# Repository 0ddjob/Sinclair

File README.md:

# Sinclair
Projects for Sinclair computers (ZX80, ZX81, TS1000, TS1500, TS2068, Spectrum and clonesn such as the Minstrel 2 & 3).

## Note
These projects maybe work-in-progress and thus not completed or fully tested!

# [TS1500 Extender](/TS1500_Extender)
The Timex Sinclair TS1500 is a 16KB ZX81/TS1000 in a Spectrum-style case.  As such the expansion port can use full-width expansions due to the power & cassette ports.  This project aims to create an extender to allow full-width expansion (i.e. ZXpand) to be used.

## Status
22-May-2025: Work in progress<br>

# [ZX80 Gaming Keyboard](/ZX80_Gaming_Keyboard)
The cursor keys on a ZX80/ZX81 are the 5/6/7/8 numeric keys along the top row.  My simple brain can't readily adapt to this in games like ZX80 KONG or PACMAN so this is just a ZX80/ZX81 compatible keyboard with additional cursor keys.  Designed initially for use with the Minstrel 2 computer (ZX80), but can also be used with the ZX80, Minstrel 3/ZX81 and Minstrel 4th/Jupiter Ace.

## Video
- [Minstrel 2 (Sinclair ZX80 Clone): Part 3 (Gaming Keyboard)](https://youtu.be/veES_CpFuDQ)
- [Gaming Keyboard for ZX80/ZX81/Minstrel/Jupiter Ace: Part 1 (Minstrel 2 Test)](https://youtu.be/O0Em2sR0H4w)

## Status
22-May-2025: Sent to PCBWAY for test boards<br>
14-Jun-2025: Tested, errors found & fixed, PCB layout will be corrected<br>
16-Jun-2025: Revised PCB layout submitted to PCBWAY for test fabrication<br>
27-Jun-2025: Rev. B keyboard tested mostly ok, dedicated RUBOUT key not working though<br>

# [ZX80 Pixel Synch](/ZX80_Pixel_Sync)
Small daughterboard to fix the [ZX80's pixel synchronisation](http://blog.tynemouthsoftware.co.uk/2022/09/minstrel-2-pixel-synchronisation-part-1.html) issue on the Minstrel 2 computer v2.8 or earlier.  I have a v2.6 board.  

## Video
[Minstrel 2 (Sinclair ZX80 Clone): Part 2 (Pixel Synch. Issue)](https://youtu.be/O-Urgigq2Vk)

## Status
7-May-2025: Sent to PCBWAY for test boards<br>
23-May-2025: Tested successfully on my Minstrel v2.6 board! Big improvement<br>
24-May-2025: Revised layout in Rev. B, handrouted like a big boy!<br>

# [ZX81 Centronics](/ZX81_Centronics)
Recreating a DIY centronics interface from German computer magazine c't.<br>

## Status
17-Sept-2023: Completed it seems, but not yet tested

# [ZX81 RAM Upgrade](/ZX81_RAM_Upgrade)
Yes, yes, it's been done many times before.  Planning a few different versions: 16KB for standard ZX81/TS1000, 32KB with vLA1, 32KB with own PLD.

## Status
10-Sept-2023: Designed & tested<br>
22-May-2025: Don't like the original design, will re-design<br>

# [Z88 Serial Port Converter (DE9-to-DB25)](/Z88_Serial_DE9-to-DB25)
I'm finally getting my hands on a Cambridge Computers Z88.  I realised that the [Universal Backpack Drive (UBPD)](https://www.soigeneris.com/universal-backpack-drive) I have for the NEC-PC8201A will also work on the Z88 but requires a converter board.  It's possible to order one from Soigeneris when you order a UBPD and there is an existing design available on [Github](https://github.com/bkw777/Z88_RS232), but I thought I'd also have a crack at it.

## Video
[Cambridge Computer Z88: Part 2 (Backpack Drive - First Attempt)](https://youtu.be/SjToMHrZwcI)

## Status
30-Jun-2025: Tested successfully<br>

# [Z88 Serial Port Converter (DE9-to-DE9)](/Z88_Serial_DE9_Converter)
Simple board to convert Z88 DE9 serial port to standard DE9 to use with Serial-to-USB converter, for example.

## Status
1-Jul-2025: Initial design<br>

# [Z88 Mechanical Keyboard](/Z88_Mechanical_Keyboard)
The original keyboard on my Z88 seems a bit flaky - let's try designing a nice, modern replacement.

## Status
25-Jul-2025: Rev. A board tested successfully, some tweaks needed.<br>

# [VDrive Serial Interface for Z88](/VDriveZ88_Serial_Converter)
Serial interface converter for the Z88 to use a VDrive.

## Status
9-Aug-2025: Initial design completed

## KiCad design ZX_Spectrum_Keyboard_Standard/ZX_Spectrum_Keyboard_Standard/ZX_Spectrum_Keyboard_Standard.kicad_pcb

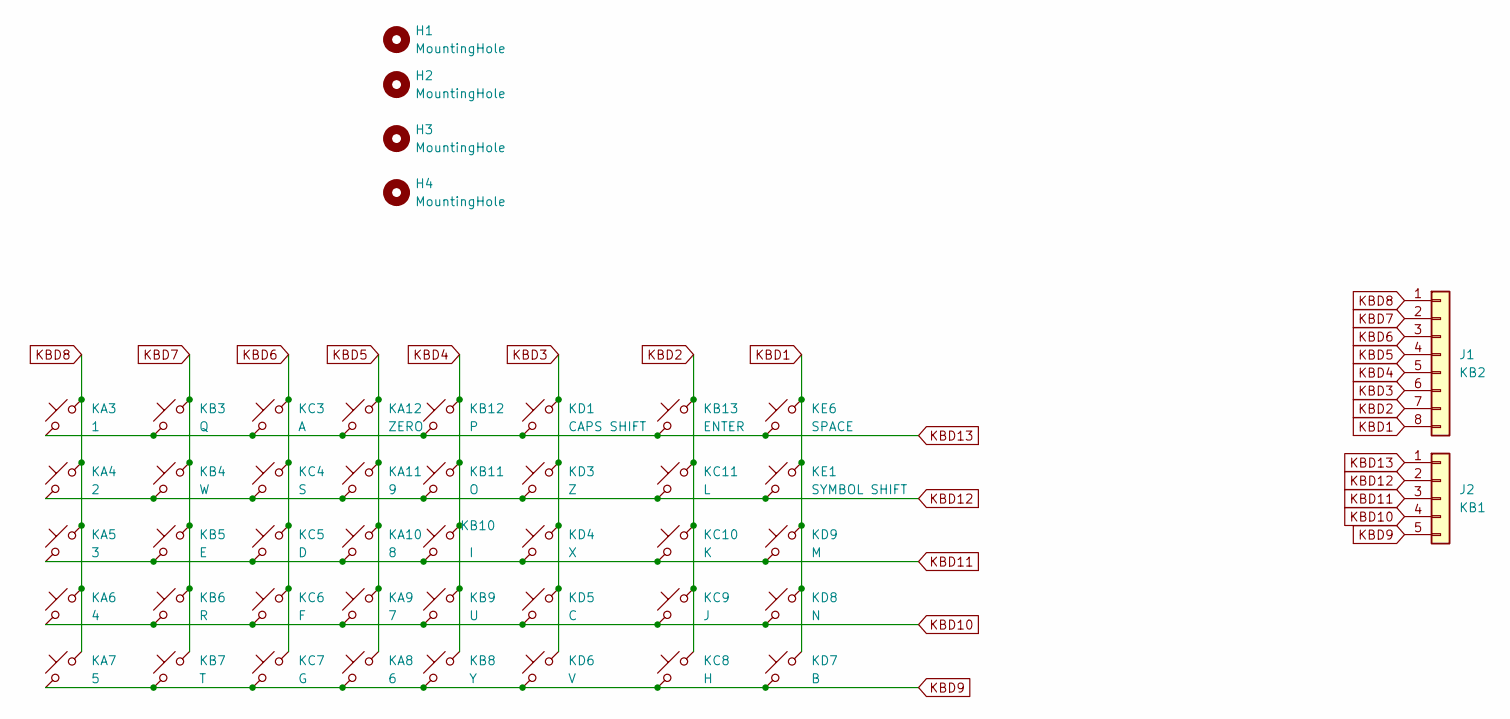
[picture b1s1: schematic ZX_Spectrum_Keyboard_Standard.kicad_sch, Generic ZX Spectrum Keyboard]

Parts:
H1, H2, H3, H4: MountingHole; MountingHole_3.2mm_M3
J1: KB2; PinHeader_1x08_P2.54mm_Vertical
J2: KB1; PinHeader_1x05_P2.54mm_Vertical
KA3: 1; SW_Gateron_LowProfile_THT
KA4: 2; SW_Gateron_LowProfile_THT
KA5: 3; SW_Gateron_LowProfile_THT
KA6: 4; SW_Gateron_LowProfile_THT
KA7: 5; SW_Gateron_LowProfile_THT
KA8: 6; SW_Gateron_LowProfile_THT
KA9: 7; SW_Gateron_LowProfile_THT
KA10: 8; SW_Gateron_LowProfile_THT
KA11: 9; SW_Gateron_LowProfile_THT
KA12: ZERO; SW_Gateron_LowProfile_THT
KB3: Q; SW_Gateron_LowProfile_THT
KB4: W; SW_Gateron_LowProfile_THT
KB5: E; SW_Gateron_LowProfile_THT
KB6: R; SW_Gateron_LowProfile_THT
KB7: T; SW_Gateron_LowProfile_THT
KB8: Y; SW_Gateron_LowProfile_THT
KB9: U; SW_Gateron_LowProfile_THT
KB10: I; SW_Gateron_LowProfile_THT
KB11: O; SW_Gateron_LowProfile_THT
KB12: P; SW_Gateron_LowProfile_THT
KB13: ENTER; SW_Gateron_LowProfile_THT
KC3: A; SW_Gateron_LowProfile_THT
KC4: S; SW_Gateron_LowProfile_THT
KC5: D; SW_Gateron_LowProfile_THT
KC6: F; SW_Gateron_LowProfile_THT
KC7: G; SW_Gateron_LowProfile_THT
KC8: H; SW_Gateron_LowProfile_THT
KC9: J; SW_Gateron_LowProfile_THT
KC10: K; SW_Gateron_LowProfile_THT
KC11: L; SW_Gateron_LowProfile_THT
KD1: CAPS SHIFT; SW_Gateron_LowProfile_THT
KD3: Z; SW_Gateron_LowProfile_THT
KD4: X; SW_Gateron_LowProfile_THT
KD5: C; SW_Gateron_LowProfile_THT
KD6: V; SW_Gateron_LowProfile_THT
KD7: B; SW_Gateron_LowProfile_THT
KD8: N; SW_Gateron_LowProfile_THT
KD9: M; SW_Gateron_LowProfile_THT
KE1: SYMBOL SHIFT; SW_Gateron_LowProfile_THT
KE6: SPACE; SW_Gateron_LowProfile_THT

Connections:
KBD1: J1.8, KD7.2, KD8.2, KD9.2, KE1.2, KE6.2
KBD2: J1.7, KB13.2, KC8.2, KC9.2, KC10.2, KC11.2
KBD3: J1.6, KD1.2, KD3.2, KD4.2, KD5.2, KD6.2
KBD4: J1.5, KB8.2, KB9.2, KB10.2, KB11.2, KB12.2
KBD5: J1.4, KA8.2, KA9.2, KA10.2, KA11.2, KA12.2
KBD6: J1.3, KC3.2, KC4.2, KC5.2, KC6.2, KC7.2
KBD7: J1.2, KB3.2, KB4.2, KB5.2, KB6.2, KB7.2
KBD8: J1.1, KA3.2, KA4.2, KA5.2, KA6.2, KA7.2
KBD9: J2.5, KA7.1, KA8.1, KB7.1, KB8.1, KC7.1, KC8.1, KD6.1, KD7.1
KBD10: J2.4, KA6.1, KA9.1, KB6.1, KB9.1, KC6.1, KC9.1, KD5.1, KD8.1
KBD11: J2.3, KA5.1, KA10.1, KB5.1, KB10.1, KC5.1, KC10.1, KD4.1, KD9.1
KBD12: J2.2, KA4.1, KA11.1, KB4.1, KB11.1, KC4.1, KC11.1, KD3.1, KE1.1
KBD13: J2.1, KA3.1, KA12.1, KB3.1, KB12.1, KB13.1, KC3.1, KD1.1, KE6.1

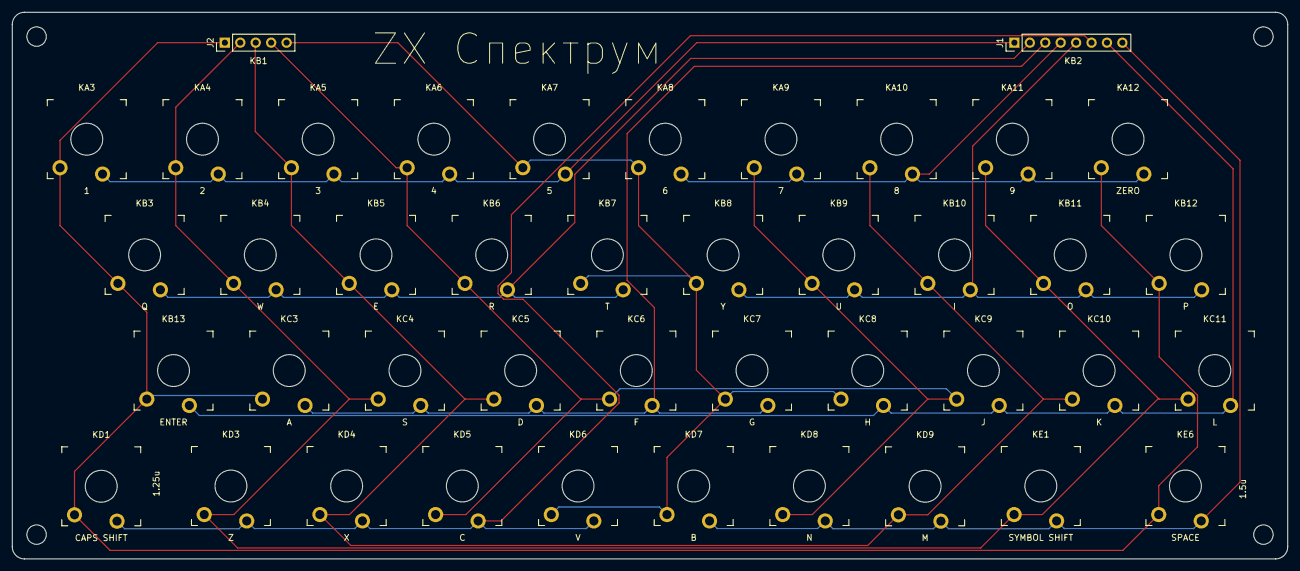
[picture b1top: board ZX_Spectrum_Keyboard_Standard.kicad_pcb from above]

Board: 2 copper layers, 210.0 x 90.0 mm, 46 parts (0 on the bottom side), 13 nets.

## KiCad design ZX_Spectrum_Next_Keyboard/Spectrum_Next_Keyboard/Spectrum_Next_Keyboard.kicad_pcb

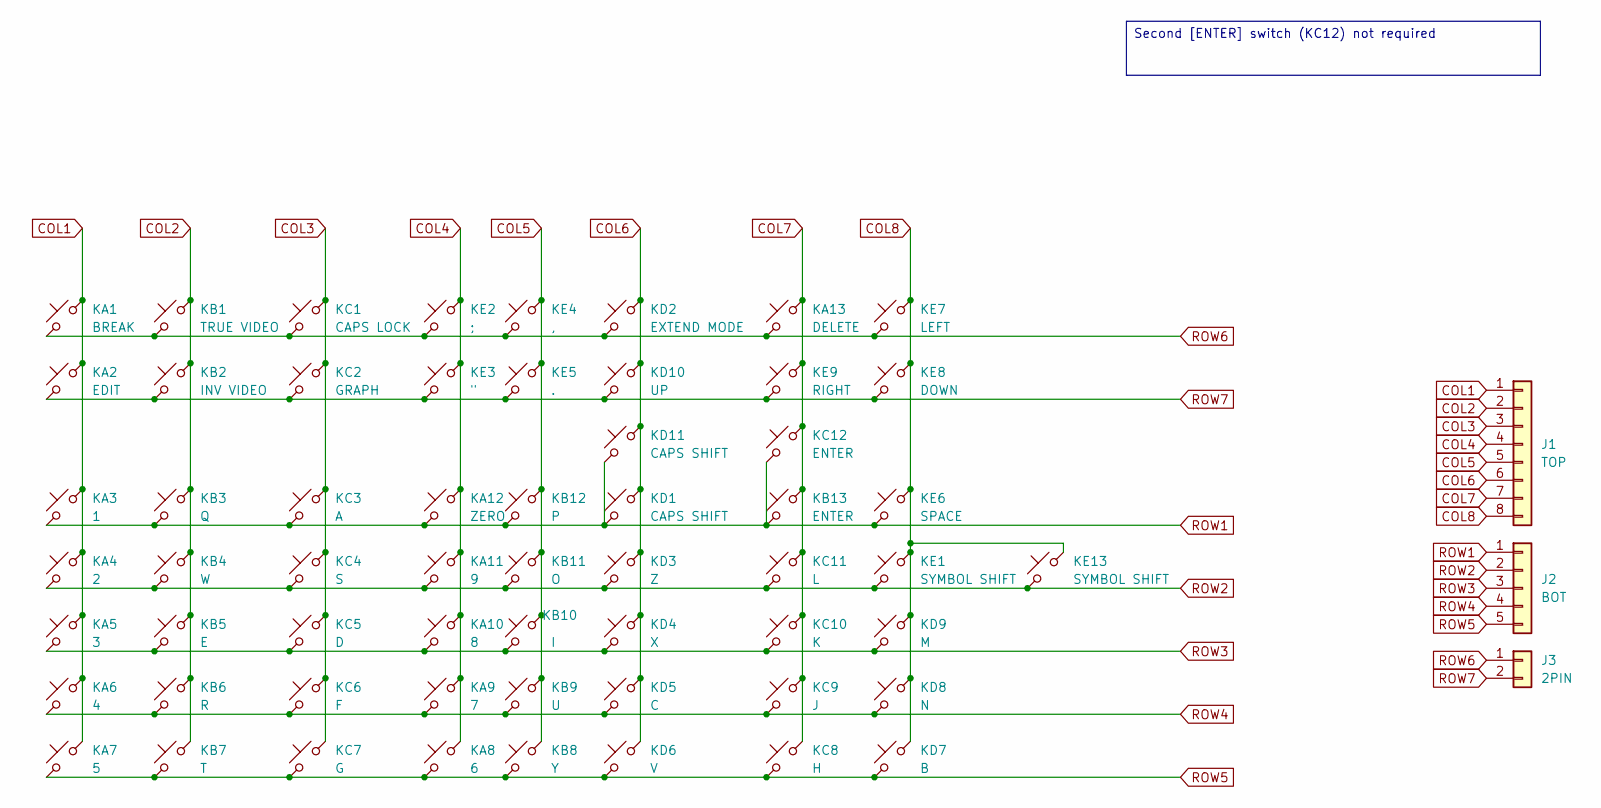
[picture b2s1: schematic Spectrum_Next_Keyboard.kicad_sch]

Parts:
J1: TOP; PinHeader_1x08_P2.54mm_Vertical
J2: BOT; PinHeader_1x05_P2.54mm_Vertical
J3: 2PIN; PinHeader_1x02_P2.54mm_Vertical
KA1: BREAK; SW_Gateron_LowProfile_THT
KA2: EDIT; SW_Gateron_LowProfile_THT
KA3: 1; SW_Gateron_LowProfile_THT
KA4: 2; SW_Gateron_LowProfile_THT
KA5: 3; SW_Gateron_LowProfile_THT
KA6: 4; SW_Gateron_LowProfile_THT
KA7: 5; SW_Gateron_LowProfile_THT
KA8: 6; SW_Gateron_LowProfile_THT
KA9: 7; SW_Gateron_LowProfile_THT
KA10: 8; SW_Gateron_LowProfile_THT
KA11: 9; SW_Gateron_LowProfile_THT
KA12: ZERO; SW_Gateron_LowProfile_THT
KA13: DELETE; SW_Gateron_LowProfile_THT
KB1: TRUE VIDEO; SW_Gateron_LowProfile_THT
KB2: INV VIDEO; SW_Gateron_LowProfile_THT
KB3: Q; SW_Gateron_LowProfile_THT
KB4: W; SW_Gateron_LowProfile_THT
KB5: E; SW_Gateron_LowProfile_THT
KB6: R; SW_Gateron_LowProfile_THT
KB7: T; SW_Gateron_LowProfile_THT
KB8: Y; SW_Gateron_LowProfile_THT
KB9: U; SW_Gateron_LowProfile_THT
KB10: I; SW_Gateron_LowProfile_THT
KB11: O; SW_Gateron_LowProfile_THT
KB12: P; SW_Gateron_LowProfile_THT
KB13: ENTER; SW_Gateron_LowProfile_THT
KC1: CAPS LOCK; SW_Gateron_LowProfile_THT
KC2: GRAPH; SW_Gateron_LowProfile_THT
KC3: A; SW_Gateron_LowProfile_THT
KC4: S; SW_Gateron_LowProfile_THT
KC5: D; SW_Gateron_LowProfile_THT
KC6: F; SW_Gateron_LowProfile_THT
KC7: G; SW_Gateron_LowProfile_THT
KC8: H; SW_Gateron_LowProfile_THT
KC9: J; SW_Gateron_LowProfile_THT
KC10: K; SW_Gateron_LowProfile_THT
KC11: L; SW_Gateron_LowProfile_THT
KC12: ENTER; SW_Gateron_LowProfile_THT
KD1, KD11: CAPS SHIFT; SW_Gateron_LowProfile_THT
KD2: EXTEND MODE; SW_Gateron_LowProfile_THT
KD3: Z; SW_Gateron_LowProfile_THT
KD4: X; SW_Gateron_LowProfile_THT
KD5: C; SW_Gateron_LowProfile_THT
KD6: V; SW_Gateron_LowProfile_THT
KD7: B; SW_Gateron_LowProfile_THT
KD8: N; SW_Gateron_LowProfile_THT
KD9: M; SW_Gateron_LowProfile_THT
KD10: UP; SW_Gateron_LowProfile_THT
KE1, KE13: SYMBOL SHIFT; SW_Gateron_LowProfile_THT
KE2: ;; SW_Gateron_LowProfile_THT
KE3: "; SW_Gateron_LowProfile_THT
KE4: ,; SW_Gateron_LowProfile_THT
KE5: .; SW_Gateron_LowProfile_THT
KE6: SPACE; SW_Gateron_LowProfile_THT
KE7: LEFT; SW_Gateron_LowProfile_THT
KE8: DOWN; SW_Gateron_LowProfile_THT
KE9: RIGHT; SW_Gateron_LowProfile_THT

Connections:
COL1: J1.1, KA1.2, KA2.2, KA3.2, KA4.2, KA5.2, KA6.2, KA7.2
COL2: J1.2, KB1.2, KB2.2, KB3.2, KB4.2, KB5.2, KB6.2, KB7.2
COL3: J1.3, KC1.2, KC2.2, KC3.2, KC4.2, KC5.2, KC6.2, KC7.2
COL4: J1.4, KA8.2, KA9.2, KA10.2, KA11.2, KA12.2, KE2.2, KE3.2
COL5: J1.5, KB8.2, KB9.2, KB10.2, KB11.2, KB12.2, KE4.2, KE5.2
COL6: J1.6, KD1.2, KD2.2, KD3.2, KD4.2, KD5.2, KD6.2, KD10.2, KD11.2
COL7: J1.7, KA13.2, KB13.2, KC8.2, KC9.2, KC10.2, KC11.2, KC12.2, KE9.2
COL8: J1.8, KD7.2, KD8.2, KD9.2, KE1.2, KE6.2, KE7.2, KE8.2, KE13.2
ROW1: J2.1, KA3.1, KA12.1, KB3.1, KB12.1, KB13.1, KC3.1, KC12.1, KD1.1, KD11.1, KE6.1
ROW2: J2.2, KA4.1, KA11.1, KB4.1, KB11.1, KC4.1, KC11.1, KD3.1, KE1.1, KE13.1
ROW3: J2.3, KA5.1, KA10.1, KB5.1, KB10.1, KC5.1, KC10.1, KD4.1, KD9.1
ROW4: J2.4, KA6.1, KA9.1, KB6.1, KB9.1, KC6.1, KC9.1, KD5.1, KD8.1
ROW5: J2.5, KA7.1, KA8.1, KB7.1, KB8.1, KC7.1, KC8.1, KD6.1, KD7.1
ROW6: J3.1, KA1.1, KA13.1, KB1.1, KC1.1, KD2.1, KE2.1, KE4.1, KE7.1
ROW7: J3.2, KA2.1, KB2.1, KC2.1, KD10.1, KE3.1, KE5.1, KE8.1, KE9.1

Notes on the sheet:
Second [ENTER] switch (KC12) not required

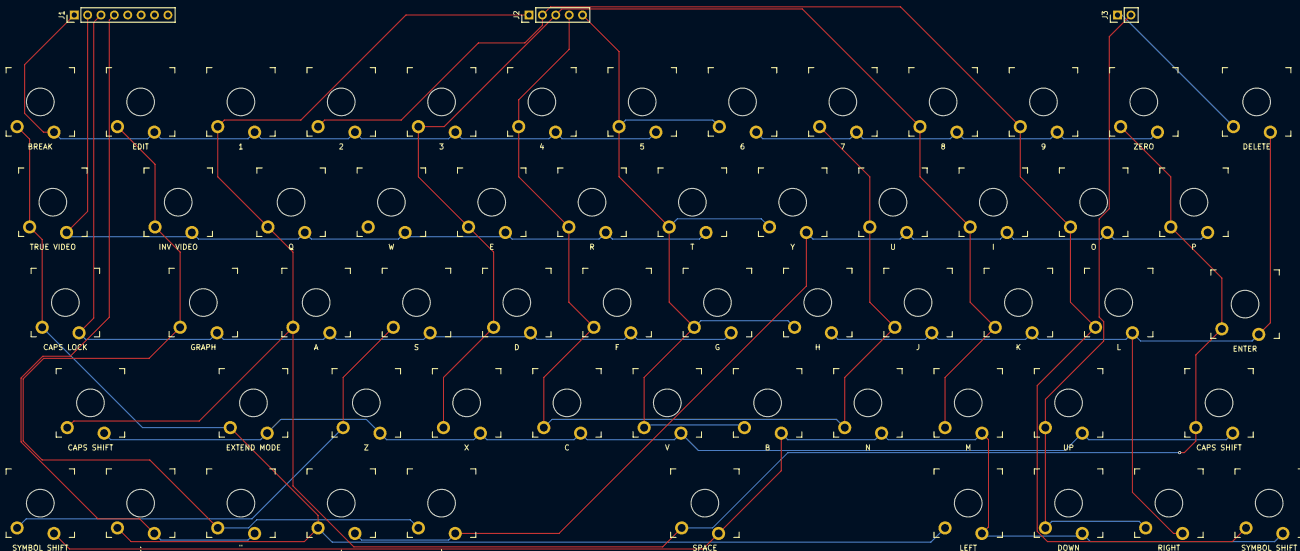
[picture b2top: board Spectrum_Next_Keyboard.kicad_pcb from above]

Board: 2 copper layers, 61 parts (0 on the bottom side), 15 nets.

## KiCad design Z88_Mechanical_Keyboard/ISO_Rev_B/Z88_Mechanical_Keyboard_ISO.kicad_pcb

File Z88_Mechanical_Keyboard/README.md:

# Z88 Mechanical Keyboard
I've not had too much luck with the keyboard on my Z88 - seems a bit flaky after 40-odd years.  So I thought I'd try to create a mechanical replacement.<br>

I've modified the layout slightly to improve the arrangement - the cursors are now a "proper" inverted-T layout.<br>

## Layout
The layout almost matches a modern set of keycaps, apart from the custom ones.<br>
By this, I mean the SHIFTED characters on each key match a modern keyboard so a generic set of key caps, plus some blanks, should work.<br>

## Changes From Original Z88 Layout
The reason for these changes are either to improve the layout (cursors) or to simplify getting key caps (CAPS LOCK & DIAMOND)
- (Rev. A) Cursors are now an inverted-T
- (Rev. B) CAPS LOCK moved to standard location between TAB and LH SHIFT and is now 1.75u (a standard size in key cap sets)
- (Rev. B) DIAMOND moved to original DOWN cursor location (bottom right) and is now 1u (can use a blank)
- (Rev. C) Possibly external version via Z88 expansion port featuring switchable on/off backlit keys ... ?

## Construction
The board is designed to use Gateron Low Profile (KS-33) type key switches with Cherry MX-style key caps.<br>

- 64 key switches (Gateron KS-33)
- 53 x 1u key caps
- 5 x 1u blank (INDEX, MENU, HELP, SQUARE, DIAMOND)
- 1 x 1.25x2u (ISO ENTER)
- 1 x 1.5u (TAB)
- 1 x 1.75u (CAPS LOCK)
- 2 x 2u (SHIFT)
- 1 x 7u (SPACE)
- (Optional) Stabiliser for 7u SPACE bar? (must work with Gateron low-profile)
- 2 x 8-pin thin film connectors (e.g. TE Connectivity/AMP 5-520314-8 or similar)
- 2 x 8-pin strips of thin film cables (e.g. Parlex PSR1635-08 or similar)

I've not been able to find suitable PCB-mount stabilisers yet.<br>

## Related Videos
- [Schematic & PCB layout](https://youtu.be/C3n-ExND1uk)
- [Track routing & final touches](https://youtu.be/aaBBvU5d50o)
- [Testing the Rev. A PCB](https://youtu.be/vxIY81ir3Ao)
- [Testing the Rev. B PCB](https://youtu.be/KMXMAZTbPG8)

## Further Work To Do 
### Rev. C
- Create an external version (no changes required to Z88) connecting via Z88 expansion port
- Z88 expansion port connector still available?

## Status
1-Jul-2025: Work in progress<br>
3-Jul-2025: Added 6.25u space bar layout<br>
4-Jul-2025: Added inverted-T cursor layout<br>
5-Jul-2025: Inverted-T cursor design routed, ready for test fabrication<br>
7-Jul-2025: Design tweaked, sent to PCBWAY for test fabrication<br>
12-Jul-2025: Test PCBs shipped from PCBWAY<br>
25-Jul-2025: Test PCBs arrived, working!!, need to adjust size of PCB slightly ... maybe (see [video](https://youtu.be/vxIY81ir3Ao))<br>
26-Jul-2025: Started work on Rev. B<br>
31-Jul-2025: Completed Rev. B changes<br>
1-Aug-2025: Submitted to PCBway<br>
5-Aug-2025: Rev. B PCBs shipped from PCBway<br>
15-Aug-2025: Rev. B test PCBs arrived & tested, almost perfect.<br>

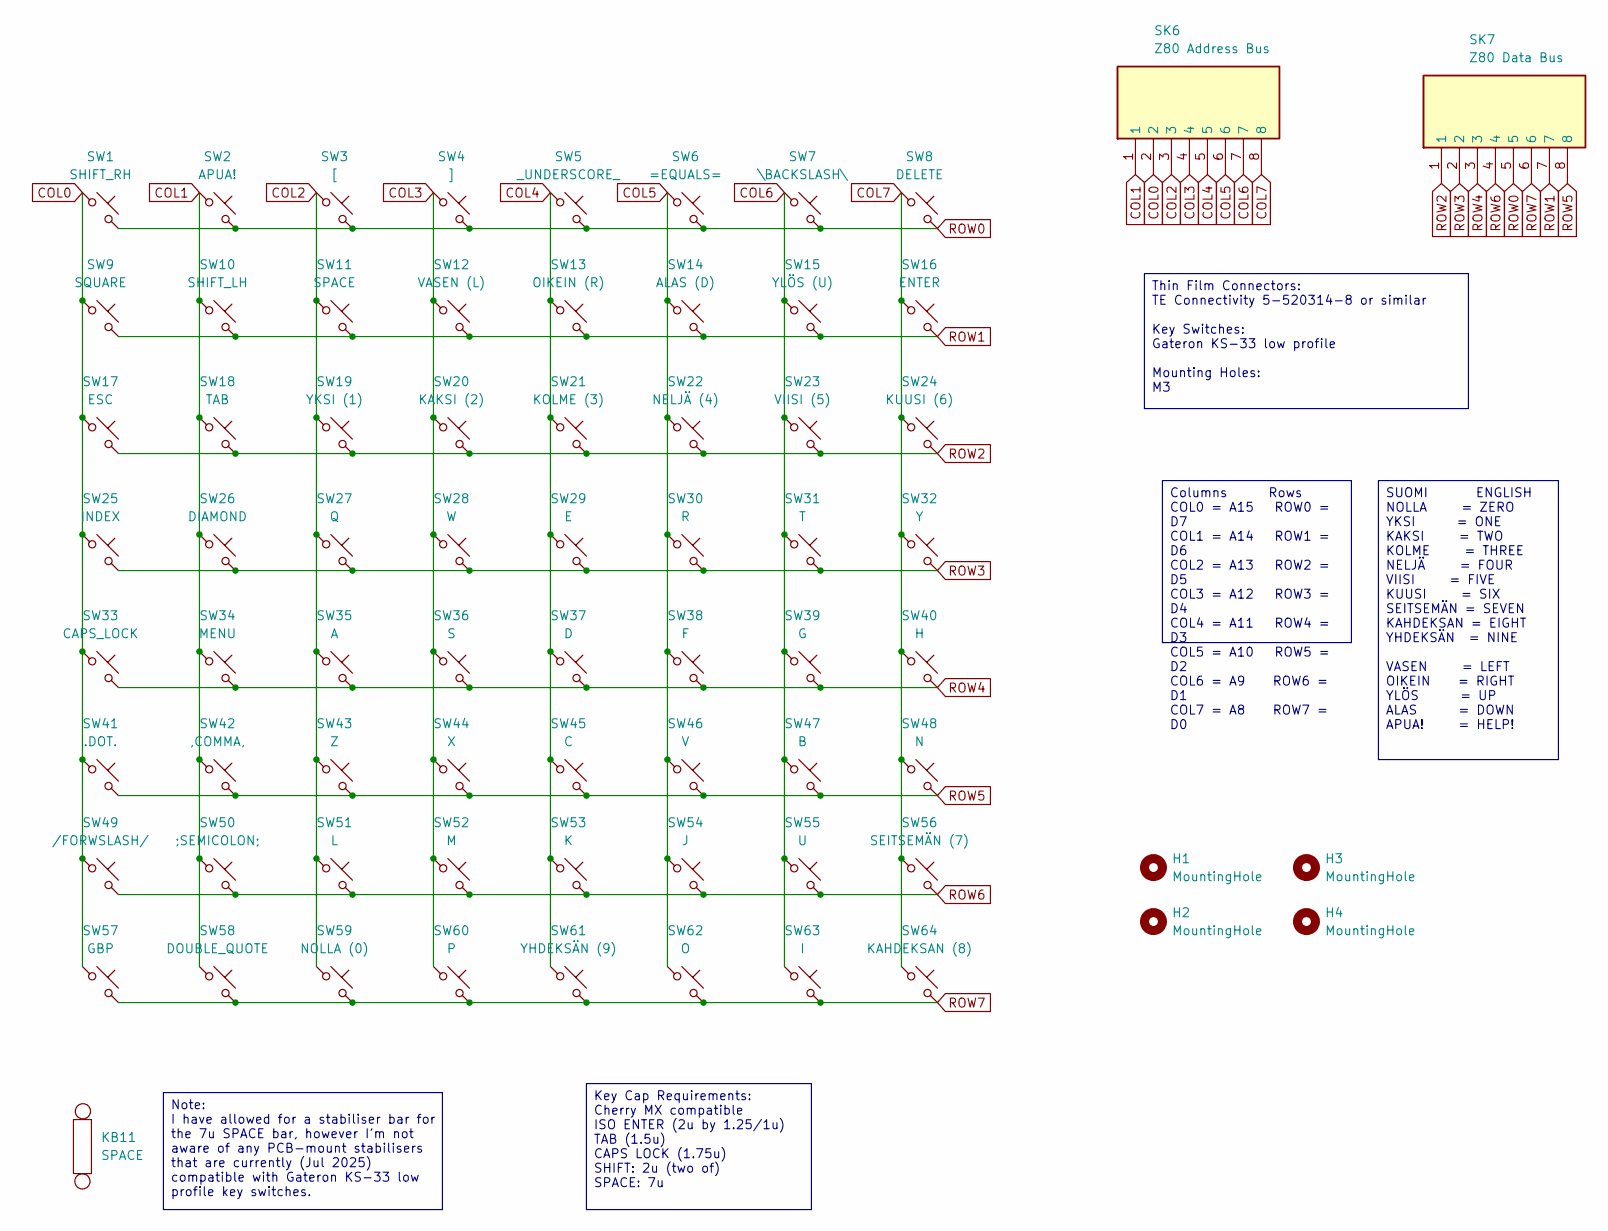
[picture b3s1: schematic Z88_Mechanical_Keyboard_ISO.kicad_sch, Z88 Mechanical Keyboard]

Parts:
H1, H2, H3, H4: MountingHole; MountingHole_3.2mm_M3
KB11: SPACE; Stabilizer_Cherry_MX_7.00u
SK6: Z80 Address Bus; 55203148; Mouser Part Number 571-5-520314-8
SK7: Z80 Data Bus; 55203148; Mouser Part Number 571-5-520314-8
SW1: SHIFT_RH; SW_Gateron_LowProfile_THT
SW2: APUA!; SW_Gateron_LowProfile_THT
SW3: [; SW_Gateron_LowProfile_THT
SW4: ]; SW_Gateron_LowProfile_THT
SW5: _UNDERSCORE_; SW_Gateron_LowProfile_THT
SW6: =EQUALS=; SW_Gateron_LowProfile_THT
SW7: \BACKSLASH\; SW_Gateron_LowProfile_THT
SW8: DELETE; SW_Gateron_LowProfile_THT
SW9: SQUARE; SW_Gateron_LowProfile_THT
SW10: SHIFT_LH; SW_Gateron_LowProfile_THT
SW11: SPACE; SW_Gateron_LowProfile_THT
SW12: VASEN (L); SW_Gateron_LowProfile_THT
SW13: OIKEIN (R); SW_Gateron_LowProfile_THT
SW14: ALAS (D); SW_Gateron_LowProfile_THT
SW15: YLÖS (U); SW_Gateron_LowProfile_THT
SW16: ENTER; SW_Gateron_LowProfile_THT
SW17: ESC; SW_Gateron_LowProfile_THT
SW18: TAB; SW_Gateron_LowProfile_THT
SW19: YKSI (1); SW_Gateron_LowProfile_THT
SW20: KAKSI (2); SW_Gateron_LowProfile_THT
SW21: KOLME (3); SW_Gateron_LowProfile_THT
SW22: NELJÄ (4); SW_Gateron_LowProfile_THT
SW23: VIISI (5); SW_Gateron_LowProfile_THT
SW24: KUUSI (6); SW_Gateron_LowProfile_THT
SW25: INDEX; SW_Gateron_LowProfile_THT
SW26: DIAMOND; SW_Gateron_LowProfile_THT
SW27: Q; SW_Gateron_LowProfile_THT
SW28: W; SW_Gateron_LowProfile_THT
SW29: E; SW_Gateron_LowProfile_THT
SW30: R; SW_Gateron_LowProfile_THT
SW31: T; SW_Gateron_LowProfile_THT
SW32: Y; SW_Gateron_LowProfile_THT
SW33: CAPS_LOCK; SW_Gateron_LowProfile_THT
SW34: MENU; SW_Gateron_LowProfile_THT
SW35: A; SW_Gateron_LowProfile_THT
SW36: S; SW_Gateron_LowProfile_THT
SW37: D; SW_Gateron_LowProfile_THT
SW38: F; SW_Gateron_LowProfile_THT
SW39: G; SW_Gateron_LowProfile_THT
SW40: H; SW_Gateron_LowProfile_THT
SW41: .DOT.; SW_Gateron_LowProfile_THT
SW42: ,COMMA,; SW_Gateron_LowProfile_THT
SW43: Z; SW_Gateron_LowProfile_THT
SW44: X; SW_Gateron_LowProfile_THT
SW45: C; SW_Gateron_LowProfile_THT
SW46: V; SW_Gateron_LowProfile_THT
SW47: B; SW_Gateron_LowProfile_THT
SW48: N; SW_Gateron_LowProfile_THT
SW49: /FORWSLASH/; SW_Gateron_LowProfile_THT
SW50: ;SEMICOLON;; SW_Gateron_LowProfile_THT
SW51: L; SW_Gateron_LowProfile_THT
SW52: M; SW_Gateron_LowProfile_THT
SW53: K; SW_Gateron_LowProfile_THT
SW54: J; SW_Gateron_LowProfile_THT
SW55: U; SW_Gateron_LowProfile_THT
SW56: SEITSEMÄN (7); SW_Gateron_LowProfile_THT
SW57: GBP; SW_Gateron_LowProfile_THT
SW58: DOUBLE_QUOTE; SW_Gateron_LowProfile_THT
SW59: NOLLA (0); SW_Gateron_LowProfile_THT
SW60: P; SW_Gateron_LowProfile_THT
SW61: YHDEKSÄN (9); SW_Gateron_LowProfile_THT
SW62: O; SW_Gateron_LowProfile_THT
SW63: I; SW_Gateron_LowProfile_THT
SW64: KAHDEKSAN (8); SW_Gateron_LowProfile_THT

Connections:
COL0: SK6.2, SW1.1, SW9.1, SW17.1, SW25.1, SW33.1, SW41.1, SW49.1, SW57.1
COL1: SK6.1, SW2.1, SW10.1, SW18.1, SW26.1, SW34.1, SW42.1, SW50.1, SW58.1
COL2: SK6.3, SW3.1, SW11.1, SW19.1, SW27.1, SW35.1, SW43.1, SW51.1, SW59.1
COL3: SK6.4, SW4.1, SW12.1, SW20.1, SW28.1, SW36.1, SW44.1, SW52.1, SW60.1
COL4: SK6.5, SW5.1, SW13.1, SW21.1, SW29.1, SW37.1, SW45.1, SW53.1, SW61.1
COL5: SK6.6, SW6.1, SW14.1, SW22.1, SW30.1, SW38.1, SW46.1, SW54.1, SW62.1
COL6: SK6.7, SW7.1, SW15.1, SW23.1, SW31.1, SW39.1, SW47.1, SW55.1, SW63.1
COL7: SK6.8, SW8.1, SW16.1, SW24.1, SW32.1, SW40.1, SW48.1, SW56.1, SW64.1
ROW0: SK7.5, SW1.2, SW2.2, SW3.2, SW4.2, SW5.2, SW6.2, SW7.2, SW8.2
ROW1: SK7.7, SW9.2, SW10.2, SW11.2, SW12.2, SW13.2, SW14.2, SW15.2, SW16.2
ROW2: SK7.1, SW17.2, SW18.2, SW19.2, SW20.2, SW21.2, SW22.2, SW23.2, SW24.2
ROW3: SK7.2, SW25.2, SW26.2, SW27.2, SW28.2, SW29.2, SW30.2, SW31.2, SW32.2
ROW4: SK7.3, SW33.2, SW34.2, SW35.2, SW36.2, SW37.2, SW38.2, SW39.2, SW40.2
ROW5: SK7.8, SW41.2, SW42.2, SW43.2, SW44.2, SW45.2, SW46.2, SW47.2, SW48.2
ROW6: SK7.4, SW49.2, SW50.2, SW51.2, SW52.2, SW53.2, SW54.2, SW55.2, SW56.2
ROW7: SK7.6, SW57.2, SW58.2, SW59.2, SW60.2, SW61.2, SW62.2, SW63.2, SW64.2

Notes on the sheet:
Note: I have allowed for a stabiliser bar for the 7u SPACE bar, however I'm not aware of any PCB-mount stabilisers that are currently (Jul 2025) compatible with Gateron KS-33 low profile key switches.
Key Cap Requirements: Cherry MX compatible ISO ENTER (2u by 1.25/1u) TAB (1.5u) CAPS LOCK (1.75u) SHIFT: 2u (two of) SPACE: 7u
Thin Film Connectors: TE Connectivity 5-520314-8 or similar Key Switches: Gateron KS-33 low profile Mounting Holes: M3
SUOMI ENGLISH NOLLA = ZERO YKSI = ONE KAKSI = TWO KOLME = THREE NELJÄ = FOUR VIISI = FIVE KUUSI = SIX SEITSEMÄN = SEVEN KAHDEKSAN = EIGHT YHDEKSÄN = NINE VASEN = LEFT OIKEIN = RIGHT YLÖS = UP ALAS = DOWN APUA! = HELP!
Columns Rows COL0 = A15 ROW0 = D7 COL1 = A14 ROW1 = D6 COL2 = A13 ROW2 = D5 COL3 = A12 ROW3 = D4 COL4 = A11 ROW4 = D3 COL5 = A10 ROW5 = D2 COL6 = A9 ROW6 = D1 COL7 = A8 ROW7 = D0

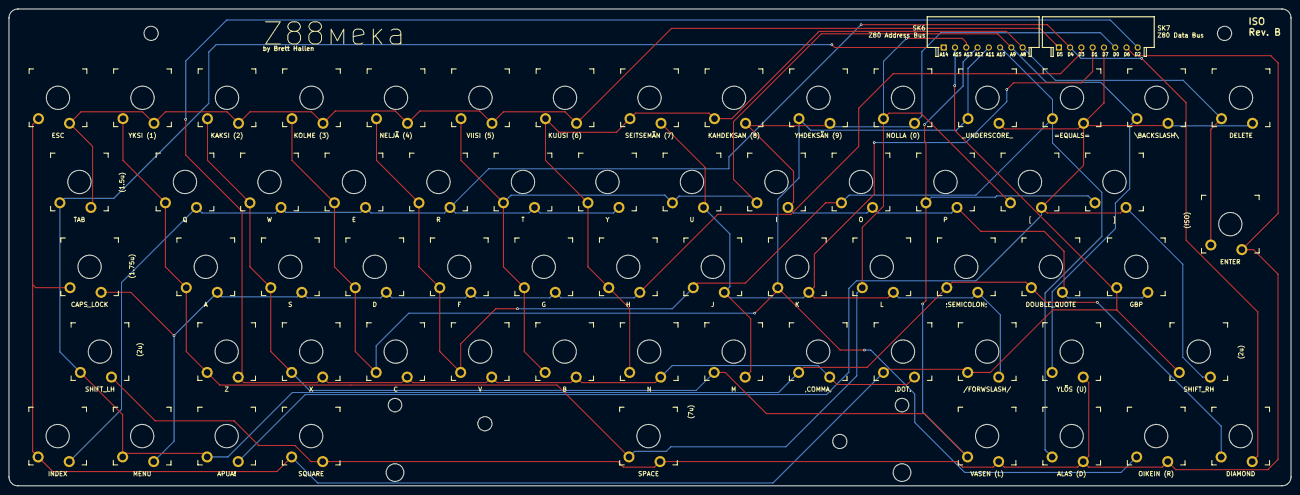
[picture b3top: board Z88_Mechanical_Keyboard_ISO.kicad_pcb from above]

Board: 2 copper layers, 289.0 x 107.5 mm, 71 parts (0 on the bottom side), 16 nets.

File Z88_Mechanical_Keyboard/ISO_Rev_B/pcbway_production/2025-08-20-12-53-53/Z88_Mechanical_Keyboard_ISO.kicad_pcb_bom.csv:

Designator,Quantity,Value,Footprint,Package,MPN,DNP,Mount_Type,Description,Height,Mouser Part Number,Mouser Price/Stock,Manufacturer_Name
KB11,1,SPACE,Stabilizer_Cherry_MX_7.00u,,,,tht,,,,,
SK6,1,Z80 Address Bus,55203148,,5-520314-8,,tht,TRIOMATE ASSY H 8P L=2.54 LDFR,4.83,571-5-520314-8,https://www.mouser.co.uk/ProductDetail/TE-Connectivity-AMP/5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,TE Connectivity
SK7,1,Z80 Data Bus,55203148,,5-520314-8,,tht,TRIOMATE ASSY H 8P L=2.54 LDFR,4.83,571-5-520314-8,https://www.mouser.co.uk/ProductDetail/TE-Connectivity-AMP/5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,TE Connectivity
SW1,1,SHIFT_RH,SW_Gateron_LowProfile_THT,,,,tht,"Push button switch, normally open, two pins, 45° tilted",,,,
SW10,1,SHIFT_LH,SW_Gateron_LowProfile_THT,,,,tht,"Push button switch, normally open, two pins, 45° tilted",,,,
SW11,1,SPACE,SW_Gateron_LowProfile_THT,,,,tht,"Push button switch, normally open, two pins, 45° tilted",,,,
SW12,1,VASEN (L),SW_Gateron_LowProfile_THT,,,,tht,"Push button switch, normally open, two pins, 45° tilted",,,,
SW13,1,OIKEIN (R),SW_Gateron_LowProfile_THT,,,,tht,"Push button switch, normally open, two pins, 45° tilted",,,,
SW14,1,ALAS (D),SW_Gateron_LowProfile_THT,,,,tht,"Push button switch, normally open, two pins, 45° tilted",,,,
SW15,1,YLÖS (U),SW_Gateron_LowProfile_THT,,,,tht,"Push button switch, normally open, two pins, 45° tilted",,,,
SW16,1,ENTER,SW_Gateron_LowProfile_THT,,,,tht,"Push button switch, normally open, two pins, 45° tilted",,,,
SW17,1,ESC,SW_Gateron_LowProfile_THT,,,,tht,"Push button switch, normally open, two pins, 45° tilted",,,,
SW18,1,TAB,SW_Gateron_LowProfile_THT,,,,tht,"Push button switch, normally open, two pins, 45° tilted",,,,
SW19,1,YKSI (1),SW_Gateron_LowProfile_THT,,,,tht,"Push button switch, normally open, two pins, 45° tilted",,,,
SW2,1,APUA!,SW_Gateron_LowProfile_THT,,,,tht,"Push button switch, normally open, two pins, 45° tilted",,,,
SW20,1,KAKSI (2),SW_Gateron_LowProfile_THT,,,,tht,"Push button switch, normally open, two pins, 45° tilted",,,,
SW21,1,KOLME (3),SW_Gateron_LowProfile_THT,,,,tht,"Push button switch, normally open, two pins, 45° tilted",,,,
SW22,1,NELJÄ (4),SW_Gateron_LowProfile_THT,,,,tht,"Push button switch, normally open, two pins, 45° tilted",,,,
SW23,1,VIISI (5),SW_Gateron_LowProfile_THT,,,,tht,"Push button switch, normally open, two pins, 45° tilted",,,,
SW24,1,KUUSI (6),SW_Gateron_LowProfile_THT,,,,tht,"Push button switch, normally open, two pins, 45° tilted",,,,
SW25,1,INDEX,SW_Gateron_LowProfile_THT,,,,tht,"Push button switch, normally open, two pins, 45° tilted",,,,
SW26,1,DIAMOND,SW_Gateron_LowProfile_THT,,,,tht,"Push button switch, normally open, two pins, 45° tilted",,,,
SW27,1,Q,SW_Gateron_LowProfile_THT,,,,tht,"Push button switch, normally open, two pins, 45° tilted",,,,
SW28,1,W,SW_Gateron_LowProfile_THT,,,,tht,"Push button switch, normally open, two pins, 45° tilted",,,,
SW29,1,E,SW_Gateron_LowProfile_THT,,,,tht,"Push button switch, normally open, two pins, 45° tilted",,,,
SW3,1,[,SW_Gateron_LowProfile_THT,,,,tht,"Push button switch, normally open, two pins, 45° tilted",,,,
SW30,1,R,SW_Gateron_LowProfile_THT,,,,tht,"Push button switch, normally open, two pins, 45° tilted",,,,
SW31,1,T,SW_Gateron_LowProfile_THT,,,,tht,"Push button switch, normally open, two pins, 45° tilted",,,,
SW32,1,Y,SW_Gateron_LowProfile_THT,,,,tht,"Push button switch, normally open, two pins, 45° tilted",,,,
SW33,1,CAPS_LOCK,SW_Gateron_LowProfile_THT,,,,tht,"Push button switch, normally open, two pins, 45° tilted",,,,
SW34,1,MENU,SW_Gateron_LowProfile_THT,,,,tht,"Push button switch, normally open, two pins, 45° tilted",,,,
SW35,1,A,SW_Gateron_LowProfile_THT,,,,tht,"Push button switch, normally open, two pins, 45° tilted",,,,
SW36,1,S,SW_Gateron_LowProfile_THT,,,,tht,"Push button switch, normally open, two pins, 45° tilted",,,,
SW37,1,D,SW_Gateron_LowProfile_THT,,,,tht,"Push button switch, normally open, two pins, 45° tilted",,,,
SW38,1,F,SW_Gateron_LowProfile_THT,,,,tht,"Push button switch, normally open, two pins, 45° tilted",,,,
SW39,1,G,SW_Gateron_LowProfile_THT,,,,tht,"Push button switch, normally open, two pins, 45° tilted",,,,
SW4,1,],SW_Gateron_LowProfile_THT,,,,tht,"Push button switch, normally open, two pins, 45° tilted",,,,
SW40,1,H,SW_Gateron_LowProfile_THT,,,,tht,"Push button switch, normally open, two pins, 45° tilted",,,,
SW41,1,.DOT.,SW_Gateron_LowProfile_THT,,,,tht,"Push button switch, normally open, two pins, 45° tilted",,,,
SW42,1,",COMMA,",SW_Gateron_LowProfile_THT,,,,tht,"Push button switch, normally open, two pins, 45° tilted",,,,
SW43,1,Z,SW_Gateron_LowProfile_THT,,,,tht,"Push button switch, normally open, two pins, 45° tilted",,,,
SW44,1,X,SW_Gateron_LowProfile_THT,,,,tht,"Push button switch, normally open, two pins, 45° tilted",,,,
SW45,1,C,SW_Gateron_LowProfile_THT,,,,tht,"Push button switch, normally open, two pins, 45° tilted",,,,
SW46,1,V,SW_Gateron_LowProfile_THT,,,,tht,"Push button switch, normally open, two pins, 45° tilted",,,,
SW47,1,B,SW_Gateron_LowProfile_THT,,,,tht,"Push button switch, normally open, two pins, 45° tilted",,,,
SW48,1,N,SW_Gateron_LowProfile_THT,,,,tht,"Push button switch, normally open, two pins, 45° tilted",,,,
SW49,1,/FORWSLASH/,SW_Gateron_LowProfile_THT,,,,tht,"Push button switch, normally open, two pins, 45° tilted",,,,
SW5,1,_UNDERSCORE_,SW_Gateron_LowProfile_THT,,,,tht,"Push button switch, normally open, two pins, 45° tilted",,,,
SW50,1,;SEMICOLON;,SW_Gateron_LowProfile_THT,,,,tht,"Push button switch, normally open, two pins, 45° tilted",,,,
SW51,1,L,SW_Gateron_LowProfile_THT,,,,tht,"Push button switch, normally open, two pins, 45° tilted",,,,
SW52,1,M,SW_Gateron_LowProfile_THT,,,,tht,"Push button switch, normally open, two pins, 45° tilted",,,,
SW53,1,K,SW_Gateron_LowProfile_THT,,,,tht,"Push button switch, normally open, two pins, 45° tilted",,,,
SW54,1,J,SW_Gateron_LowProfile_THT,,,,tht,"Push button switch, normally open, two pins, 45° tilted",,,,
SW55,1,U,SW_Gateron_LowProfile_THT,,,,tht,"Push button switch, normally open, two pins, 45° tilted",,,,
SW56,1,SEITSEMÄN (7),SW_Gateron_LowProfile_THT,,,,tht,"Push button switch, normally open, two pins, 45° tilted",,,,
SW57,1,GBP,SW_Gateron_LowProfile_THT,,,,tht,"Push button switch, normally open, two pins, 45° tilted",,,,
SW58,1,DOUBLE_QUOTE,SW_Gateron_LowProfile_THT,,,,tht,"Push button switch, normally open, two pins, 45° tilted",,,,
SW59,1,NOLLA (0),SW_Gateron_LowProfile_THT,,,,tht,"Push button switch, normally open, two pins, 45° tilted",,,,
SW6,1,=EQUALS=,SW_Gateron_LowProfile_THT,,,,tht,"Push button switch, normally open, two pins, 45° tilted",,,,
SW60,1,P,SW_Gateron_LowProfile_THT,,,,tht,"Push button switch, normally open, two pins, 45° tilted",,,,
SW61,1,YHDEKSÄN (9),SW_Gateron_LowProfile_THT,,,,tht,"Push button switch, normally open, two pins, 45° tilted",,,,
SW62,1,O,SW_Gateron_LowProfile_THT,,,,tht,"Push button switch, normally open, two pins, 45° tilted",,,,
SW63,1,I,SW_Gateron_LowProfile_THT,,,,tht,"Push button switch, normally open, two pins, 45° tilted",,,,
SW64,1,KAHDEKSAN (8),SW_Gateron_LowProfile_THT,,,,tht,"Push button switch, normally open, two pins, 45° tilted",,,,
SW7,1,\BACKSLASH\,SW_Gateron_LowProfile_THT,,,,tht,"Push button switch, normally open, two pins, 45° tilted",,,,
SW8,1,DELETE,SW_Gateron_LowProfile_THT,,,,tht,"Push button switch, normally open, two pins, 45° tilted",,,,
SW9,1,SQUARE,SW_Gateron_LowProfile_THT,,,,tht,"Push button switch, normally open, two pins, 45° tilted",,,,

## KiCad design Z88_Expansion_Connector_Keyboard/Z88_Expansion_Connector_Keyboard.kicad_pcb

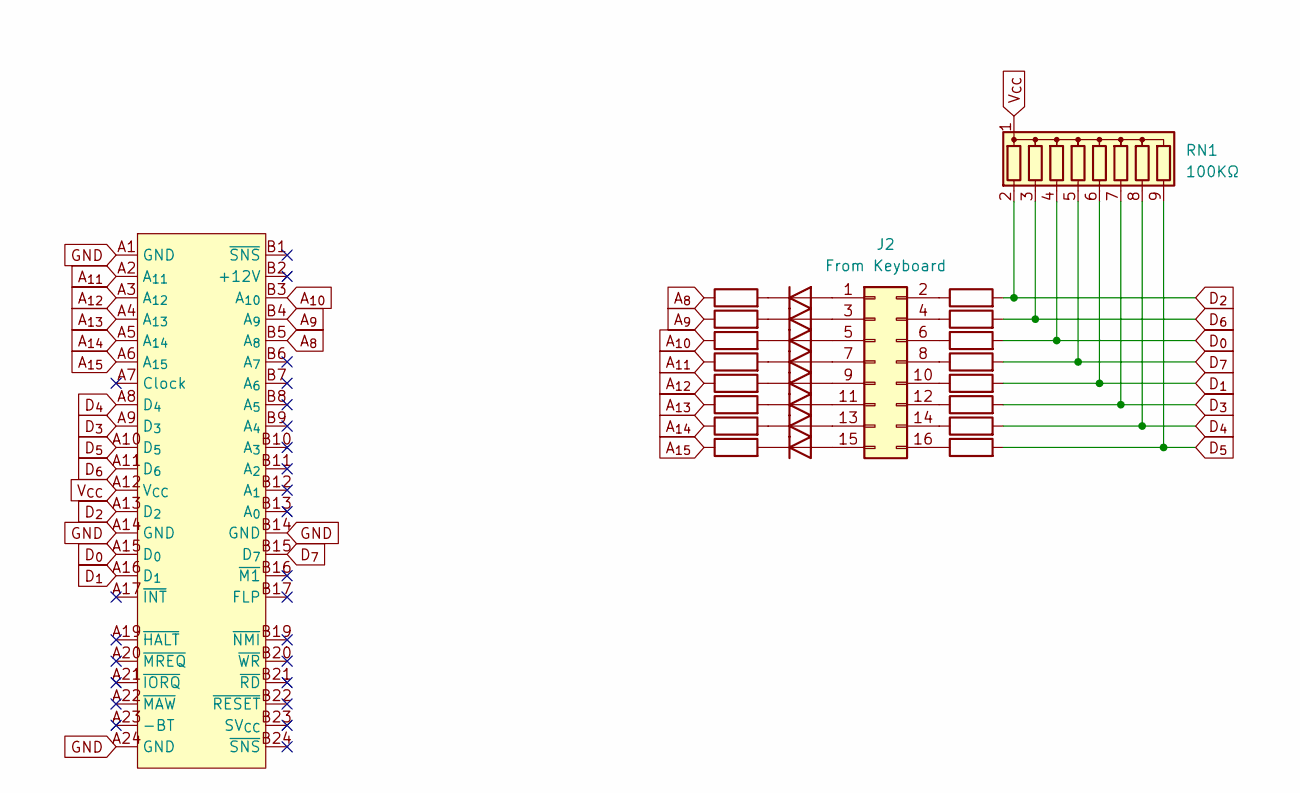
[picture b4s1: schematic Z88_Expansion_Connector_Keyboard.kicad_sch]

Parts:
D1, D2, D3, D4, D5, D6, D7, D8: 1N4148; D_DO-35_SOD27_P7.62mm_Horizontal
J1: Z88 Expansion Connector
J2: From Keyboard; PinHeader_2x08_P2.54mm_Vertical
R1, R2, R3, R4, R5, R6, R7, R8: 2.2KΩ; R_Axial_DIN0207_L6.3mm_D2.5mm_P7.62mm_Horizontal
R9, R10, R11, R12, R13, R14, R15, R16: 47KΩ; R_Axial_DIN0207_L6.3mm_D2.5mm_P7.62mm_Horizontal
RN1: 100KΩ; R_Array_SIP9

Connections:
A_{8}: J1.B5 (A_{8}), R1.1
A_{9}: J1.B4 (A_{9}), R2.1
A_{10}: J1.B3 (A_{10}), R3.1
A_{11}: J1.A2 (A_{11}), R4.1
A_{12}: J1.A3 (A_{12}), R5.1
A_{13}: J1.A4 (A_{13}), R6.1
A_{14}: J1.A5 (A_{14}), R7.1
A_{15}: J1.A6 (A_{15}), R8.1
D_{0}: J1.A15 (D_{0}), R11.2, RN1.4 (R3)
D_{1}: J1.A16 (D_{1}), R13.2, RN1.6 (R5)
D_{2}: J1.A13 (D_{2}), R9.2, RN1.2 (R1)
D_{3}: J1.A9 (D_{3}), R14.2, RN1.7 (R6)
D_{4}: J1.A8 (D_{4}), R15.2, RN1.8 (R7)
D_{5}: J1.A10 (D_{5}), R16.2, RN1.9 (R8)
D_{6}: J1.A11 (D_{6}), R10.2, RN1.3 (R2)
D_{7}: J1.B15 (D_{7}), R12.2, RN1.5 (R4)
GND: J1.A1 (GND), J1.A14 (GND), J1.A24 (GND), J1.B14 (GND)
unnamed: D1.2 (A), J2.1
unnamed: D1.1 (K), R1.2
unnamed: D2.2 (A), J2.3
unnamed: D2.1 (K), R2.2
unnamed: D3.2 (A), J2.5
unnamed: D3.1 (K), R3.2
unnamed: D4.2 (A), J2.7
unnamed: D4.1 (K), R4.2
unnamed: D5.2 (A), J2.9
unnamed: D5.1 (K), R5.2
unnamed: D6.2 (A), J2.11
unnamed: D6.1 (K), R6.2
unnamed: D7.2 (A), J2.13
unnamed: D7.1 (K), R7.2
unnamed: D8.2 (A), J2.15
unnamed: D8.1 (K), R8.2
unnamed: J2.2, R9.1
unnamed: J2.4, R10.1
unnamed: J2.6, R11.1
unnamed: J2.8, R12.1
unnamed: J2.10, R13.1
unnamed: J2.12, R14.1
unnamed: J2.14, R15.1
unnamed: J2.16, R16.1
V_{CC}: J1.A12 (V_{CC}), RN1.1 (common)
